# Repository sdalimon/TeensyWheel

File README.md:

# TeensyWheel
A replacement PCB for the Flashfire ForceWheel WH2304-V gaming wheel

I bought the Flashfire ForceWheel WH2304-V because it was low cost, but found the button configuration annoying.  There are a lot of buttons, but many of them are shared with other functions (like the paddles and gearshift) leaving few usable ones.  Some of this was configurable, but it had to be done each time the unit was plugged in.

I knew a Teensy can act as a joystick so looked into using one as a replacement controller.  It didn't turn out that hard.  Most of the time was spent measuring the button and mounting hole locations on the original PCB to be sure the replecement would fit.

A bit of code later and now all buttons are indiviually mapped to joystick inputs.  

It works well, but I haven't used it a lot since I am having trouble with the button mapping in American Truck Simulator. They all show up and work in the Windows control panel.  You can change the button mapping in the software (Look at the end of IO_Pins.h)

The software does not implement the vibration or USB host features.

Sorry there isn't a BOM, but most of the parts were scavanged off the original PCB or are generic surface mount parts.

When ordering PCBs make sure they are 1.2 mm thick.

Documenation - PDF schematics, Assembly drawings and some reverse engineering of the original PCB
Output - Gerbers
Software - The Arduino project for the software - using with Arduino and TeensyDuino
Libraries - The local KiCad libraries

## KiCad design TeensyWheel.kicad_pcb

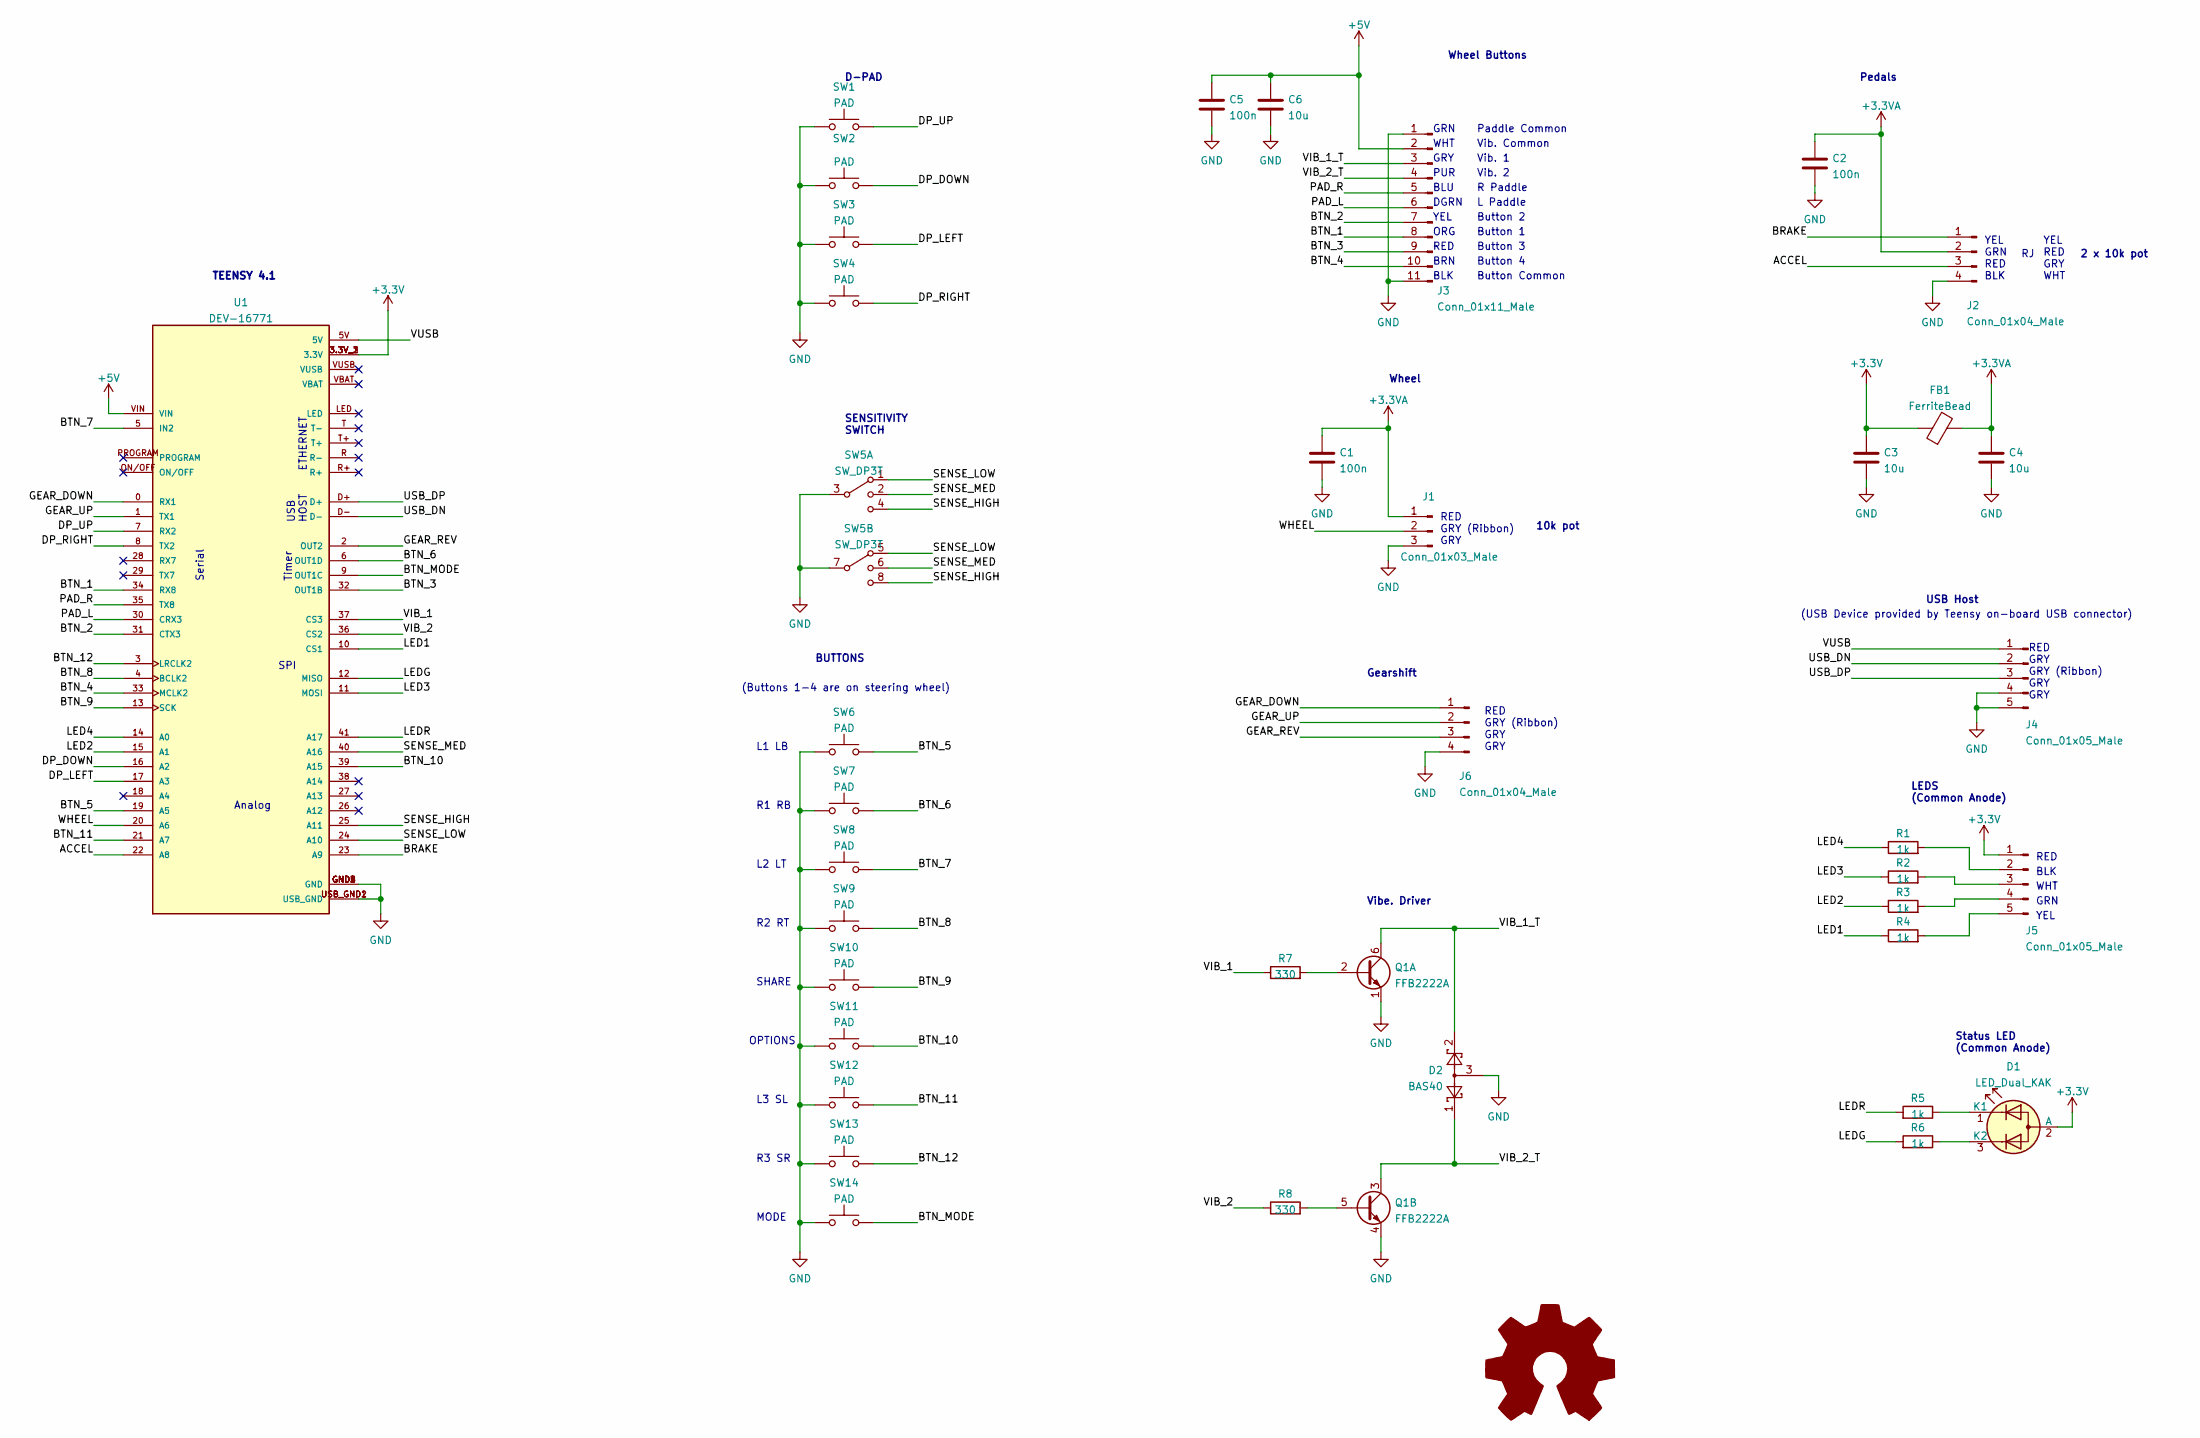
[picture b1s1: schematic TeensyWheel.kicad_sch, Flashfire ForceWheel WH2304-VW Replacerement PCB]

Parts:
C1, C2, C5: 100n; C_0603_1608Metric_Pad1.08x0.95mm_HandSolder
C3, C4, C6: 10u; C_0603_1608Metric_Pad1.08x0.95mm_HandSolder
D1: LED_Dual_KAK; LED_D3.0mm-3
D2: BAS40; SOT-23
FB1: FerriteBead; L_0805_2012Metric_Pad1.05x1.20mm_HandSolder
J1: Conn_01x03_Male; JST_EH_B3B-EH-A_1x03_P2.50mm_Vertical
J2, J6: Conn_01x04_Male; JST_EH_B4B-EH-A_1x04_P2.50mm_Vertical
J3: Conn_01x11_Male; JST_PH_B11B-PH-K_1x11_P2.00mm_Vertical
J4, J5: Conn_01x05_Male; JST_EH_B5B-EH-A_1x05_P2.50mm_Vertical
Q1: FFB2222A; SOT-363_SC-70-6
R1, R2, R3, R4, R5, R6: 1k; R_0603_1608Metric_Pad0.98x0.95mm_HandSolder
R7, R8: 330; R_0603_1608Metric_Pad0.98x0.95mm_HandSolder
SW1, SW2, SW3, SW4, SW6, SW7, SW8, SW9, SW10, SW11, SW12, SW13, SW14: PAD; Sw_PAD_6.5mm
SW5: SW_DP3T; Sense_Sw
U1: DEV-16771; MODULE_DEV-16771; PARTREV 4.1

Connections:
+3.3VA: C1.1, C2.1, C4.1, FB1.2, J1.1, J2.2
+3V3: C3.1, D1.2 (A), FB1.1, J5.1, U1.3.3V_1 (3.3V), U1.3.3V_2 (3.3V), U1.3.3V_3 (3.3V)
+5V: C5.1, C6.1, J3.2, U1.VIN
/ACCEL: J2.3, U1.22 (A8)
/BRAKE: J2.1, U1.23 (A9)
/BTN_1: J3.8, U1.34 (RX8)
/BTN_2: J3.9, U1.32 (OUT1B)
/BTN_3: J3.7, U1.31 (CTX3)
/BTN_4: J3.10, U1.33 (MCLK2)
/BTN_5: SW6.2, U1.19 (A5)
/BTN_6: SW7.2, U1.6 (OUT1D)
/BTN_7: SW8.2, U1.5 (IN2)
/BTN_8: SW9.2, U1.4 (BCLK2)
/BTN_9: SW10.2, U1.13 (SCK)
/BTN_10: SW11.2, U1.39 (A15)
/BTN_11: SW12.2, U1.21 (A7)
/BTN_12: SW13.2, U1.3 (LRCLK2)
/BTN_MODE: SW14.2, U1.9 (OUT1C)
/DP_DOWN: SW2.2, U1.16 (A2)
/DP_LEFT: SW3.2, U1.17 (A3)
/DP_RIGHT: SW4.2, U1.8 (TX2)
/DP_UP: SW1.2, U1.7 (RX2)
/GEAR_DOWN: J6.1, U1.0 (RX1)
/GEAR_REV: J6.3, U1.2 (OUT2)
/GEAR_UP: J6.2, U1.1 (TX1)
/LED1: R4.1, U1.10 (CS1)
/LED2: R3.1, U1.15 (A1)
/LED3: R2.1, U1.11 (MOSI)
/LED4: R1.1, U1.14 (A0)
/LEDG: R6.2, U1.12 (MISO)
/LEDR: R5.2, U1.41 (A17)
/PAD_L: J3.6, U1.30 (CRX3)
/PAD_R: J3.5, U1.35 (TX8)
/SENSE_HIGH: SW5.4, SW5.8, U1.25 (A11)
/SENSE_LOW: SW5.1, SW5.5, U1.24 (A10)
/SENSE_MED: SW5.2, SW5.6, U1.40 (A16)
/USB_DN: J4.2, U1.D-
/USB_DP: J4.3, U1.D+
/VIB_1: R7.1, U1.37 (CS3)
/VIB_1_T: D2.2, J3.3, Q1.6 (C1)
/VIB_2: R8.1, U1.36 (CS2)
/VIB_2_T: D2.1, J3.4, Q1.3 (C2)
/VUSB: J4.1, U1.5V
/WHEEL: J1.2, U1.20 (A6)
GND: C1.2, C2.2, C3.2, C4.2, C5.2, C6.2, D2.3, J1.3, J2.4, J3.1, J3.11, J4.4, J4.5, J6.4, Q1.1 (E1), Q1.4 (E2), SW1.1, SW2.1, SW3.1, SW4.1, SW5.3, SW5.7, SW6.1, SW7.1, SW8.1, SW9.1, SW10.1, SW11.1, SW12.1, SW13.1, SW14.1, U1.GND1 (GND), U1.GND2 (GND), U1.GND3 (GND), U1.GND4 (GND), U1.GND5 (GND), U1.USB_GND1 (USB_GND), U1.USB_GND2 (USB_GND)
unnamed: D1.1 (K1), R5.1
unnamed: D1.3 (K2), R6.1
unnamed: J5.2, R1.2
unnamed: J5.3, R2.2
unnamed: J5.4, R3.2
unnamed: J5.5, R4.2
unnamed: Q1.2 (B1), R7.2
unnamed: Q1.5 (B2), R8.2

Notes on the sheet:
Vib. 1
GRY
D-PAD
GRN
BLK
ETHERNET
ORG
RED
YEL
YEL GRN RED BLK
WHT
USB HOST
SHARE
Gearshift
Serial
R Paddle
L3 SL
Wheel
Button 1
Vibe. Driver
BRN
USB Host
(Buttons 1-4 are on steering wheel)
10k pot
PUR
Pedals
Button Common
SPI
L2 LT
L1 LB
2 x 10k pot
R3 SR
L Paddle
Button 2
Wheel Buttons
OPTIONS
Button 3
DGRN
MODE
R1 RB

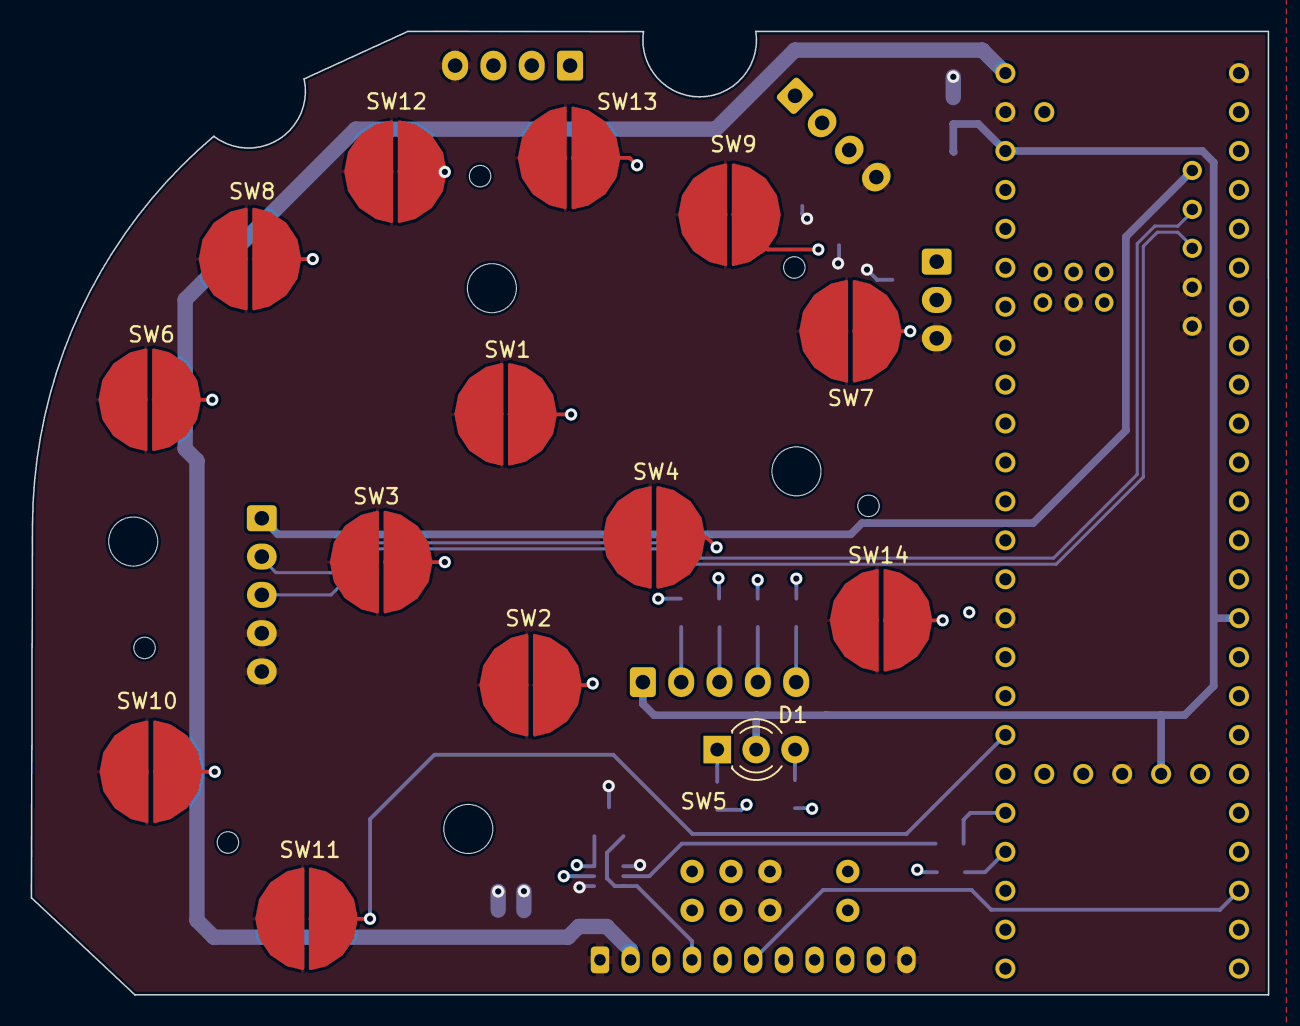
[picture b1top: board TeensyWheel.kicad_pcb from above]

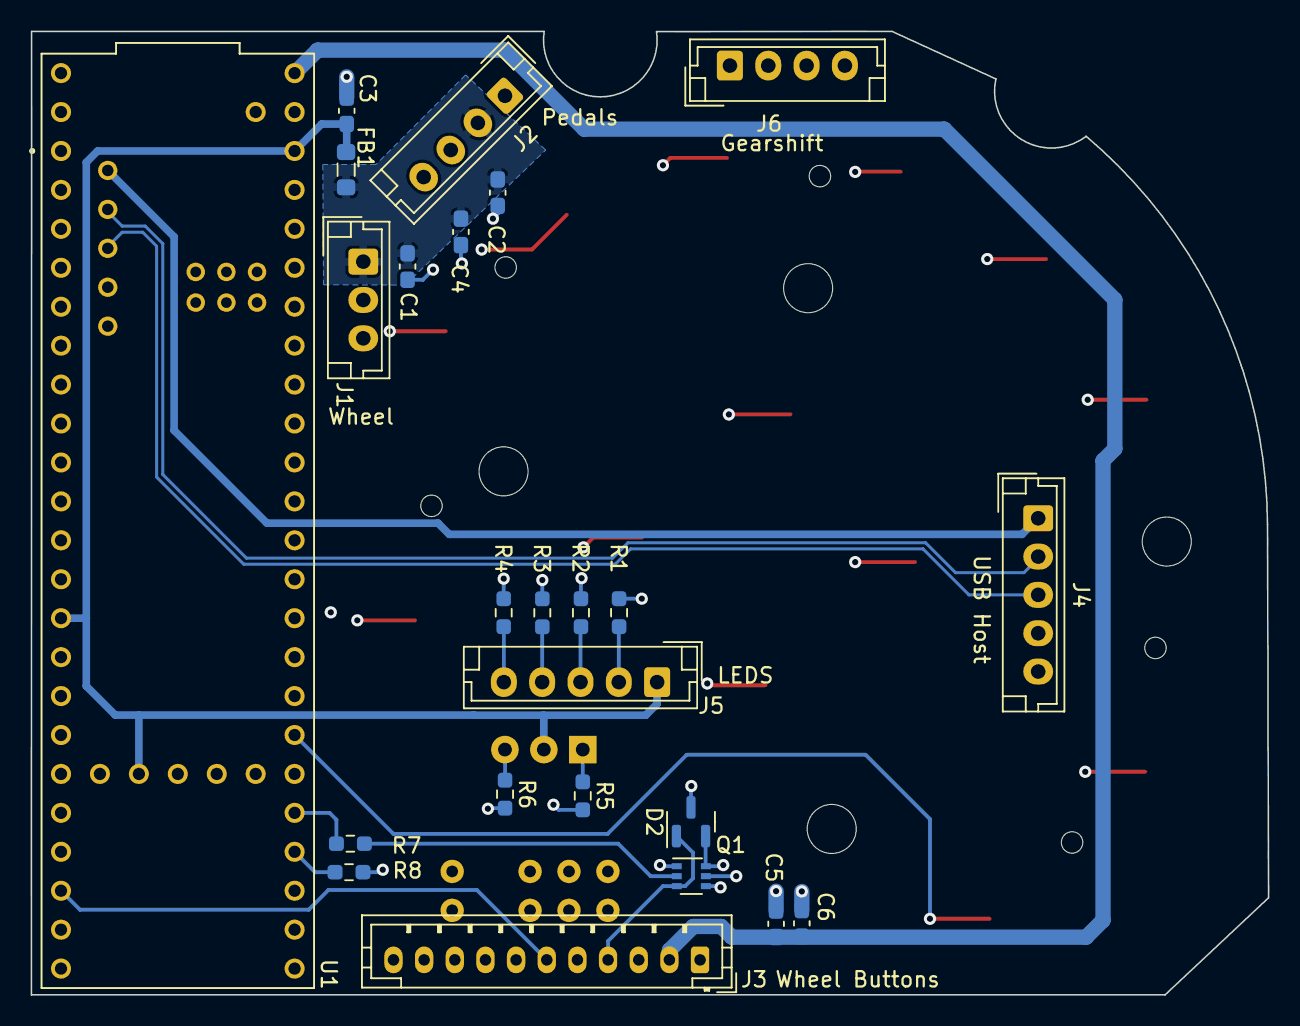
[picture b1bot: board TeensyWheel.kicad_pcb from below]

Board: 4 copper layers, 80.7 x 62.8 mm, 39 parts (24 on the bottom side), 53 nets.

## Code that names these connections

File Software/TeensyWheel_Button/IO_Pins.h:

#ifndef IO_PINS_H
#define IO_PINS_H

// IO Assignments

// Analog Inputs
const int WHEEL      = A6; // Wheel
const int ACCEL      = A8; // Pedals
const int BRAKE      = A9; // Pedals

// Digital Inputs
const int DP_UP      =  7; // D Pad
const int DP_DOWN    = 16; // D Pad
const int DP_LEFT    = 17; // D Pad
const int DP_RIGHT   =  8; // D Padd
const int PAD_R      = 35; // Paddles
const int PAD_L      = 30; // Paddles
const int GEAR_UP    =  1; // Gearshift
const int GEAR_DOWN  =  0; // Gearshift
const int GEAR_REV   =  2; // Gearshift
const int BTN_1      = 34; // Wheel Buttons
const int BTN_2      = 31; // Wheel Buttons
const int BTN_3      = 32; // Wheel Buttons
const int BTN_4      = 33; // Wheel Buttons
const int BTN_5      = 19; // L1 LB Button
const int BTN_6      =  6; // R1 RB Button
const int BTN_7      =  5; // L2 LT Button
const int BTN_8      =  4; // R2 RT Button
const int BTN_9      = 13; // SHARE Button - Oops conflicts with LED.  I hope i still works.
const int BTN_10     = 39; // OPTIONS Button
const int BTN_11     = 21; // L3 SL Button
const int BTN_12     =  3; // R3 SR Button
const int BTN_MODE   =  9; // MODE Button
const int SENSE_HIGH = 25; // Sensitivity Switch
const int SENSE_MED  = 40; // Sensitivity Switch
const int SENSE_LOW  = 24; // Sensitivity Switch

// Digital Outputs
const int LED1       = 10; // Wheel LEDS
const int LED2       = 15; // Wheel LEDs
const int LED3       = 11; // Wheel LEDs
const int LED4       = 14; // Wheel LEDs
const int LEDR       = 41; // Bicolour status LED
const int LEDG       = 12; // Bicolour status LED
const int VIB_1      = 37; // Vibrator Control
const int VIB_2      = 36; // Vibrator Control

// Input to Windows Joystick button mapping {Button 0 Input, Button 1 Input, ...}
const int NUM_BTNS = 18;
const int BTN_MAP[NUM_BTNS] = {BTN_1, BTN_2, BTN_3, BTN_4, BTN_5, BTN_6, BTN_7, BTN_8, BTN_9, BTN_10, BTN_11, BTN_12, \
                               BTN_MODE, GEAR_UP, GEAR_DOWN, GEAR_REV, SENSE_HIGH, SENSE_LOW};
#endif

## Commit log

2021-12-30 Update README.md
    Original Readme
2021-12-30 First upload
